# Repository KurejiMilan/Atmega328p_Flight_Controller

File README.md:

# Atmega328p_Flight_Controller
This repository holds all code base of flight controller implemented with atmega328p.

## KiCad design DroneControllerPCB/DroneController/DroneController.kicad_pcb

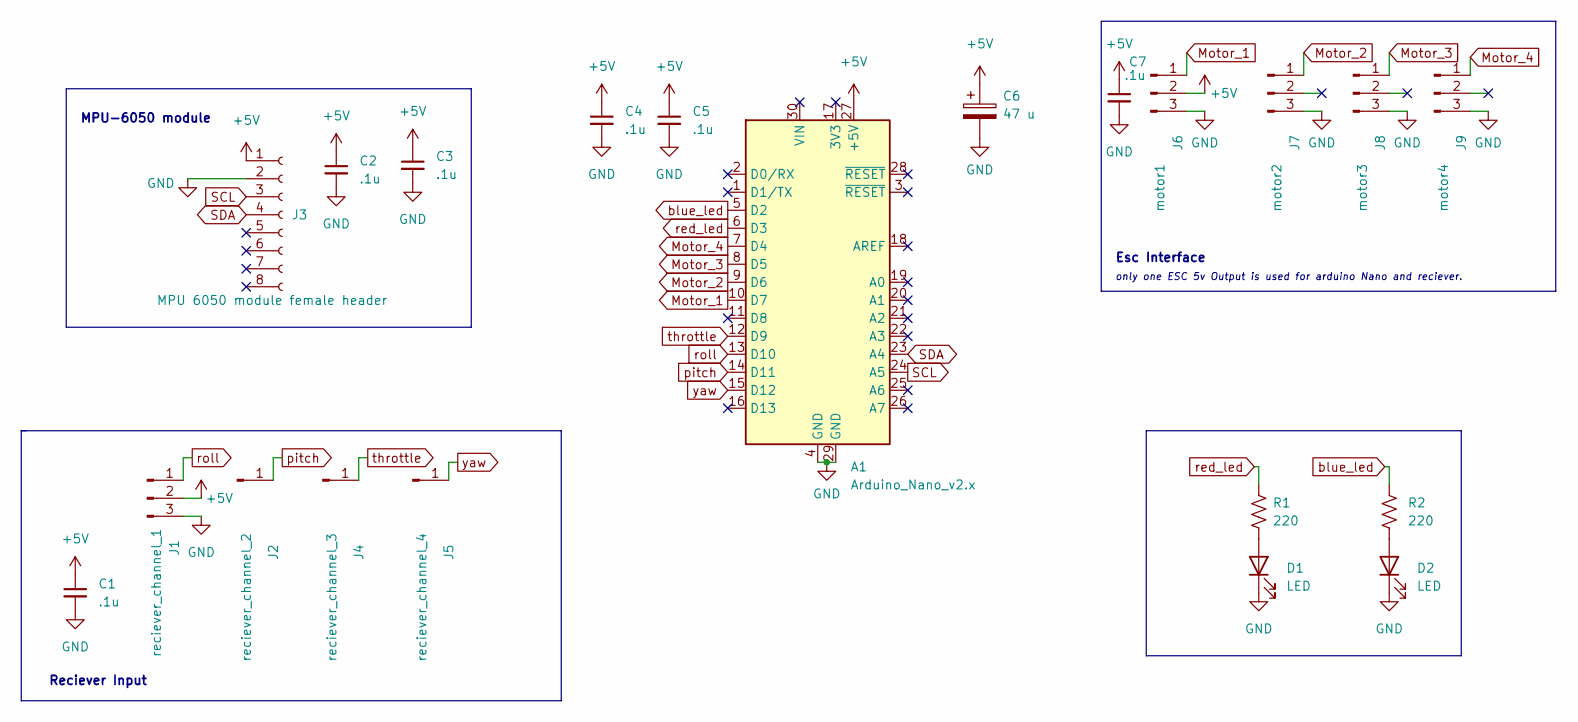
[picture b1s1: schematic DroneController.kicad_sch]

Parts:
A1: Arduino_Nano_v2.x; Arduino_Nano_modified0
C1, C2, C3, C4, C5, C7: .1u; C_Disc_D5.0mm_W2.5mm_P2.50mm
C6: 47 u; CP_Radial_D5.0mm_P2.50mm
D1, D2: LED; LED_D3.0mm_FlatTop
J1: reciever_channel_1; PinHeader_1x03_P2.54mm_Vertical_modified
J2: reciever_channel_2; PinHeader_1x01_P2.54mm_Vertical_modified
J3: MPU 6050 module female header; PinSocket_1x08_P2.54mm_Vertical_modified
J4: reciever_channel_3; PinHeader_1x01_P2.54mm_Vertical_modified
J5: reciever_channel_4; PinHeader_1x01_P2.54mm_Vertical_modified
J6: motor1; PinHeader_1x03_P2.54mm_Vertical_modified
J7: motor2; PinHeader_1x03_P2.54mm_Vertical_modified
J8: motor3; PinHeader_1x03_P2.54mm_Vertical_modified
J9: motor4; PinHeader_1x03_P2.54mm_Vertical_modified
R1, R2: 220; R_Axial_DIN0207_L6.3mm_D2.5mm_P10.16mm_Horizontal

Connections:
+5V: A1.27 (+5V), C1.1, C2.1, C3.1, C4.1, C5.1, C6.1, C7.1, J1.2, J3.1, J6.2
GND: A1.4 (GND), A1.29 (GND), C1.2, C2.2, C3.2, C4.2, C5.2, C6.2, C7.2, D1.1 (K), D2.1 (K), J1.3, J3.2, J6.3, J7.3, J8.3, J9.3
Motor_1: A1.10 (D7), J6.1
Motor_2: A1.9 (D6), J7.1
Motor_3: A1.8 (D5), J8.1
Motor_4: A1.7 (D4), J9.1
unnamed: D1.2 (A), R1.1
unnamed: D2.2 (A), R2.1
SCL: A1.24 (A5), J3.3
SDA: A1.23 (A4), J3.4
blue_led: A1.5 (D2), R2.2
pitch: A1.14 (D11), J2.1
red_led: A1.6 (D3), R1.2
roll: A1.13 (D10), J1.1
throttle: A1.12 (D9), J4.1
yaw: A1.15 (D12), J5.1

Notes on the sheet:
Esc Interface
Reciever Input
only one ESC 5v Output is used for arduino Nano and reciever.
MPU-6050 module

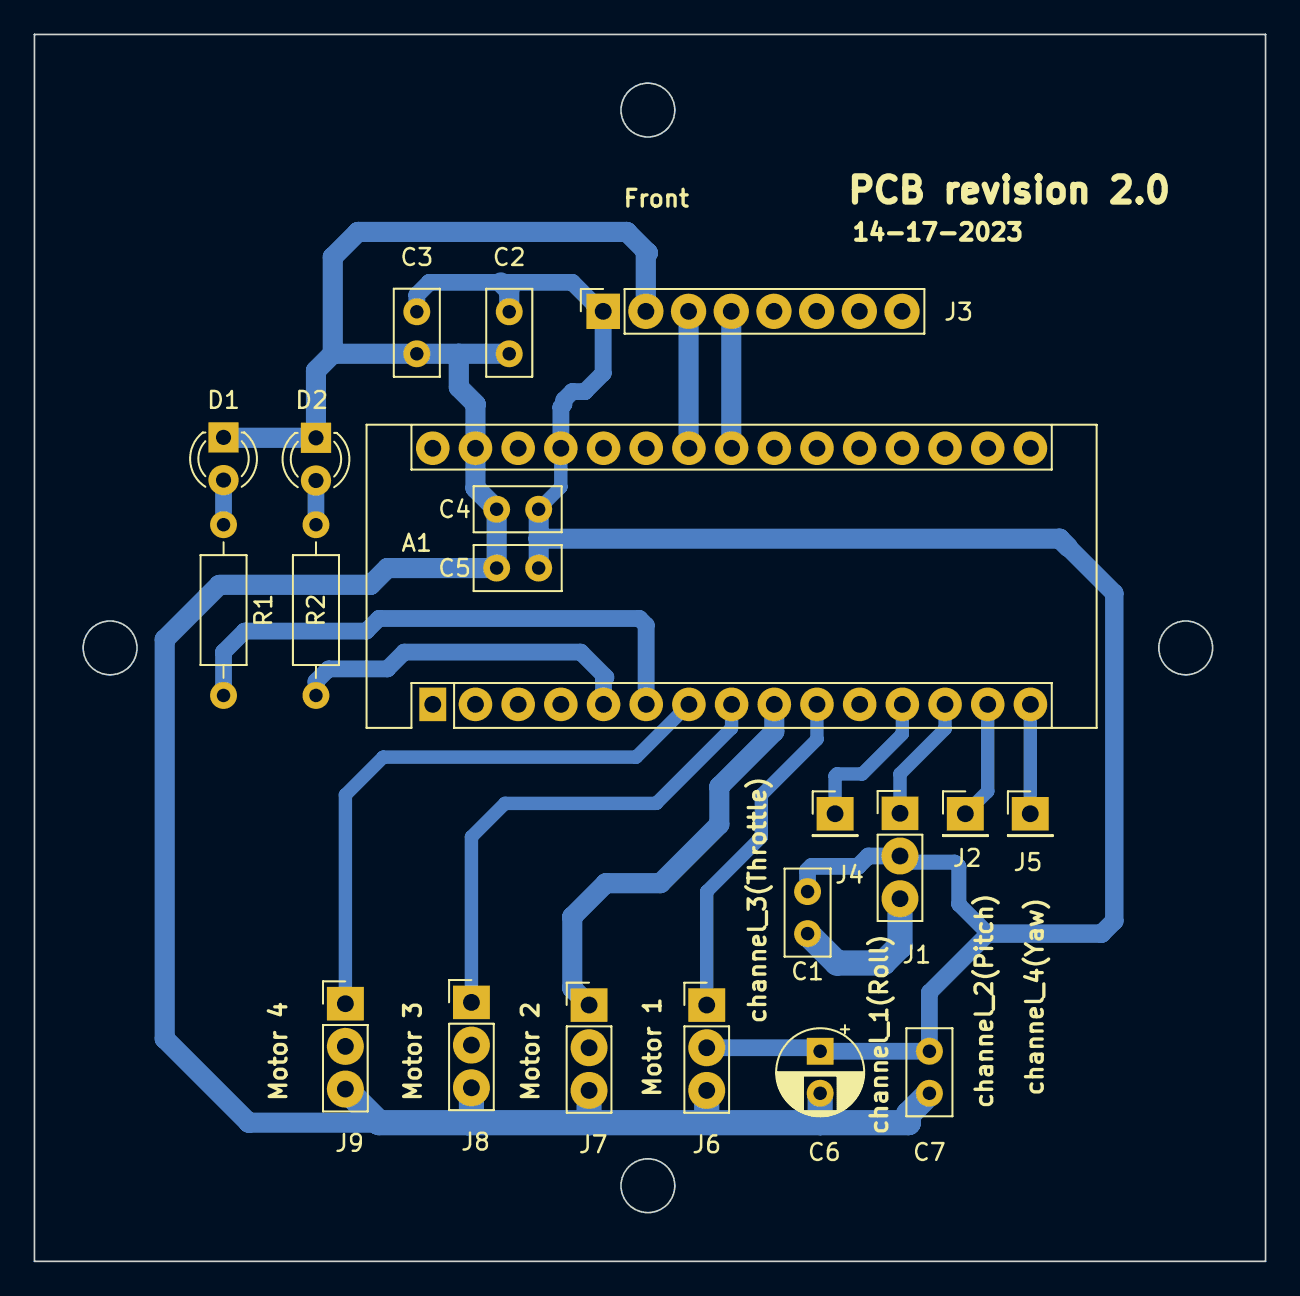
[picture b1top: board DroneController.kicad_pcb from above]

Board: 2 copper layers, 73.2 x 73.0 mm, 21 parts (0 on the bottom side), 16 nets.

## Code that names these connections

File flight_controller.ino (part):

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/* Variables used for PID calculation*/
uint32_t current_loop_micro, prev_loop_micro, loop_time = 0;                                                         // these are used for PID calculation

float pRoll = 2, pPitch = pRoll, pYaw = 0;                                                                // defining PID gains for Roll, Pitch and Yaw
float iRoll = 0, iPitch = iRoll, iYaw = 0;
float dRoll = 0, dPitch = dRoll, dYaw = 0;

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
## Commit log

2023-07-09 fight working code commit with no PID gains set to 0
2023-07-22 fuctionlaity tested readt for pid tuning
2023-07-22 Kicad files added
